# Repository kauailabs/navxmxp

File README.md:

# navX-MXP and navX-Micro Robotics Navigation Sensors
For all documentation and support for navX-MXP, please visit the [navX-MXP Wiki](http://navx-mxp.kauailabs.com).
<p>
For all documentation and support for navX-Micro, please visit the [navX-Micro Wiki](http://navx-micro.kauailabs.com).
<p>
Latest Release Notes are [here](https://github.com/kauailabs/navxmxp/blob/master/ReleaseNotes.md).

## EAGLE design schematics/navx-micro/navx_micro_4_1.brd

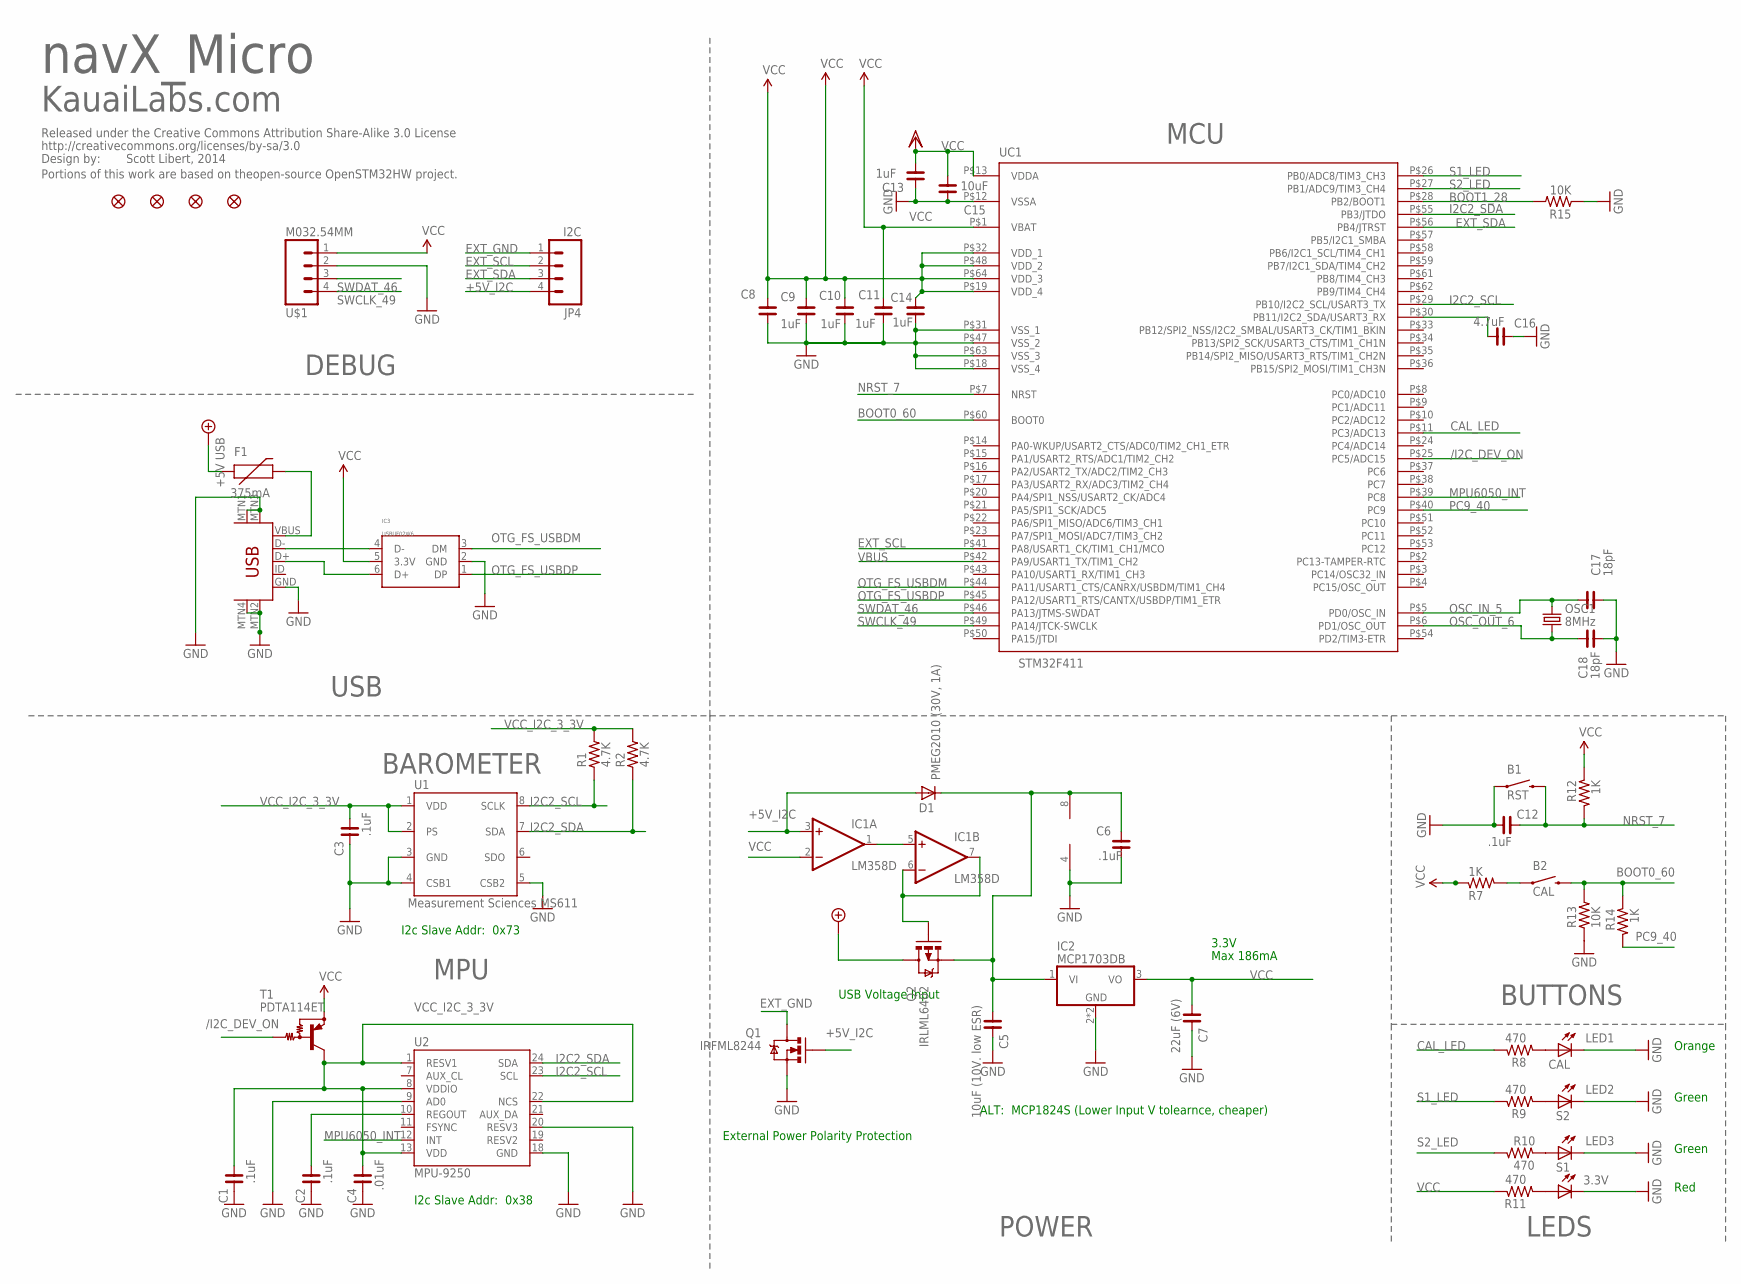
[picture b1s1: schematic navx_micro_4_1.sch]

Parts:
B1: RST; TACTILE-SWITCH-1101NE
B2: CAL; TACTILE-SWITCH-1101NE
C1, C2, C6, C12: .1uF; C0603
C3: .1uF; C0603; DIGIKEY_PART_NUMBER 399-1096-1-ND
C4: .01uF; C0603
C5: 10uF (10V. low ESR); C0805; DIGIKEY_PART_NUMBER 399-1158-1-ND
C7: 22uF (6V); C0805; DIGIKEY_PART_NUMBER 399-1158-1-ND
C8: 1uF; C0603; DIGIKEY_PART_NUMBER 399-3118-1-ND
C9, C10, C11, C13, C14: 1uF; C0603
C15: 10uF; C0805
C16: 4.7uF; C0603
C17, C18: 18pF; C0603
D1: PMEG2010 (30V, 1A); SOD-323
F1: 375mA; 0603
IC1: LM358D; SO08
IC2: MCP1703DB; DIGIKEY_PART_NUMBER MCP1703T-3302E/DBCT-ND
IC3: USBUF02W6; SC70-6; DIGIKEY_PART_NUMBER 497-3743-1-ND
JP4: I2C; 1X04
JP21, JP22, JP23, JP24: FIDUCIAL1X2; FIDUCIAL-1X2
LED1: CAL; CHIP-LED0603
LED2: S2; CHIP-LED0603
LED3: S1; CHIP-LED0603
LED4: 3.3V; CHIP-LED0603
LICENSE_TEXT: CREATIVE_COMMONS
OSC1: 8MHz; CRYSTAL-SMD-5X3
Q1: IRFML8244; SOT23; DIGIKEY_PART_NUMBER DMN3404LDICT-ND
Q2: IRLML6402; SOT23-3
R1, R2: 4.7K; R0603
R7, R12, R14: 1K; R0603
R8, R9, R10, R11: 470; R0603
R13, R15: 10K; R0603
T1: PDTA114ET; SOT23-3
U1: Measurement Sciences MS611; MS5611; DIGIKEY_PART_NUMBER MPL115A2-ND
U2: MPU-9250; QFN24_3MM_INVENSENSE; DIGIKEY_PART_NUMBER 1428-1019-1-ND
U$1: M032.54MM; 1X04_NO_SILK
UC1: STM32F411; TQFP-10X10-64; DIGIKEY_PART_NUMBER 497-11154-ND
USB: Mini-USB; USB-MINIB; DIGIKEY_PART_NUMBER 151-1206-1-ND

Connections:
+5V: F1.1, Q2.3 (D)
+5V_I2C: D1.A, IC1.3 (+IN), JP4.4, Q1.1 (G)
/I2C_DEV_ON: T1.1 (B), UC1.P$25 (PC5/ADC15)
BOOT0_60: B2.P$2 (2), R13.2, R14.1, UC1.P$60 (BOOT0)
BOOT1_28: R15.2, UC1.P$28 (PB2/BOOT1)
CAL_LED: R8.1, UC1.P$11 (PC3/ADC13)
EXT_GND: JP4.1, Q1.3 (D)
EXT_SCL: JP4.2, UC1.P$41 (PA8/USART1_CK/TIM1_CH1/MCO)
EXT_SDA: JP4.3, UC1.P$56 (PB4/JTRST)
GND: B1.P$1 (1), C1.2, C2.2, C3.2, C4.2, C5.2, C6.1, C7.2, C8.1, C9.1, C10.1, C11.1, C12.1, C13.1, C14.1, C15.2, C16.1, C17.1, C18.1, IC1.4 (V-), IC2.2 (GND), IC2.4 (GND), IC3.2 (GND), LED1.C, LED2.C, LED3.C, LED4.C, Q1.2 (S), R13.1, R15.1, U1.3 (GND), U1.4 (CSB1), U1.5 (CSB2), U2.9 (AD0), U2.18 (GND), U2.20 (RESV3), U$1.2, UC1.P$12 (VSSA), UC1.P$18 (VSS_4), UC1.P$31 (VSS_1), UC1.P$47 (VSS_2), UC1.P$63 (VSS_3), USB.GND, USB.MTN1 (MTN2), USB.MTN2 (MTN3), USB.MTN3 (MTN1), USB.MTN4
I2C2_SCL: R1.1, U1.8 (SCLK), U2.23 (SCL), UC1.P$29 (PB10/I2C2_SCL/USART3_TX)
I2C2_SDA: R2.1, U1.7 (SDA), U2.24 (SDA), UC1.P$55 (PB3/JTDO)
MPU6050_INT: U2.12 (INT), UC1.P$39 (PC8)
unnamed: C2.1, U2.10 (REGOUT)
unnamed: B2.P$1 (1), R7.2
unnamed: LED3.A, R10.1
unnamed: C16.2, UC1.P$30 (PB11/I2C2_SDA/USART3_RX)
unnamed: LED2.A, R9.2
unnamed: C5.1, C6.2, D1.C, IC1.8 (V+), IC2.1 (VI), Q2.2 (S)
unnamed: IC1.1 (OUT), IC1.5 (+IN)
unnamed: IC1.6 (-IN), IC1.7 (OUT), Q2.1 (G)
unnamed: LED1.A, R8.2
unnamed: IC3.4 (D-), USB.D-
unnamed: IC3.6 (D+), USB.D+
unnamed: LED4.A, R11.2
NRST_7: B1.P$2 (2), C12.2, R12.2, UC1.P$7 (NRST)
OSC_IN_5: C17.2, OSC1.3 (2), UC1.P$5 (PD0/OSC_IN)
OSC_OUT_6: C18.2, OSC1.1, UC1.P$6 (PD1/OSC_OUT)
OTG_FS_USBDM: IC3.3 (DM), UC1.P$44 (PA11/USART1_CTS/CANRX/USBDM/TIM1_CH4)
OTG_FS_USBDP: IC3.1 (DP), UC1.P$45 (PA12/USART1_RTS/CANTX/USBDP/TIM1_ETR)
PC9_40: R14.2, UC1.P$40 (PC9)
S1_LED: R9.1, UC1.P$26 (PB0/ADC8/TIM3_CH3)
S2_LED: R10.2, UC1.P$27 (PB1/ADC9/TIM3_CH4)
SWCLK_49: U$1.4, UC1.P$49 (PA14/JTCK-SWCLK)
SWDAT_46: U$1.3, UC1.P$46 (PA13/JTMS-SWDAT)
VBUS: F1.2, UC1.P$42 (PA9/USART1_TX/TIM1_CH2), USB.VBUS
VCC: C7.1, C8.2, C9.2, C10.2, C11.2, C13.2, C14.2, C15.1, IC1.2 (-IN), IC2.3 (VO), IC3.5 (3.3V), R7.1, R11.1, R12.1, T1.2 (E), U$1.1, UC1.P$1 (VBAT), UC1.P$13 (VDDA), UC1.P$19 (VDD_4), UC1.P$32 (VDD_1), UC1.P$48 (VDD_2), UC1.P$64 (VDD_3)
VCC_I2C_3_3V: C1.1, C3.1, C4.1, R1.2, R2.2, T1.3 (C), U1.1 (VDD), U1.2 (PS), U2.1 (RESV1), U2.8 (VDDIO), U2.13 (VDD), U2.22 (NCS)

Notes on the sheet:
BAROMETER
MPU
3.3V
Max 186mA
POWER
BUTTONS
LEDS
USB
MCU
KauaiLabs.com
Scott Libert, 2014
Portions of this work are based on theopen-source OpenSTM32HW project.
navX_Micro
I2c Slave Addr: 0x38
I2c Slave Addr: 0x73
ALT: MCP1824S (Lower Input V tolearnce, cheaper)
Orange
Green
Red
USB Voltage Input
DEBUG
External Power Polarity Protection

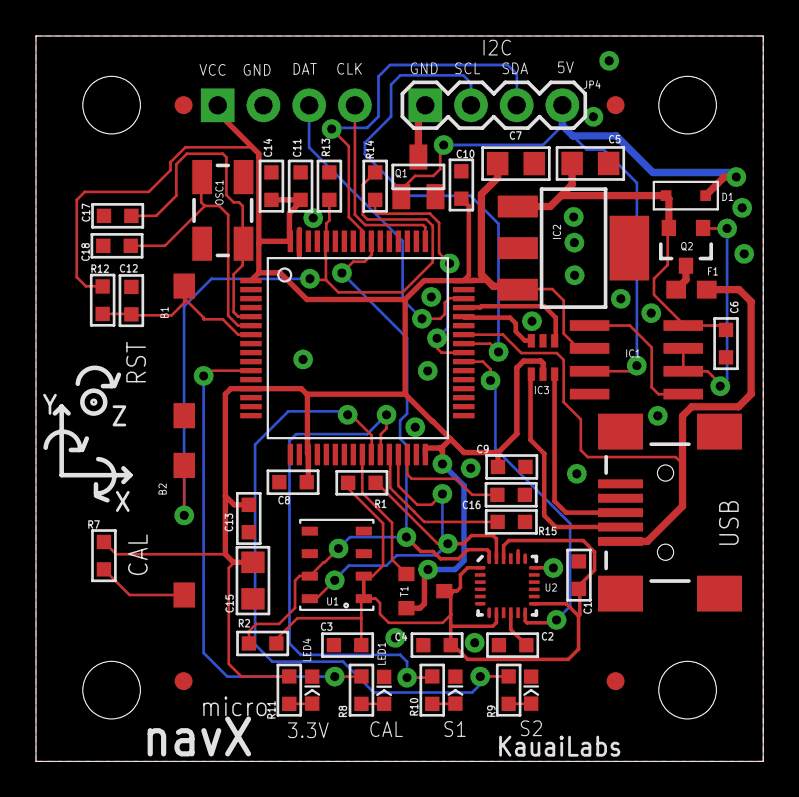
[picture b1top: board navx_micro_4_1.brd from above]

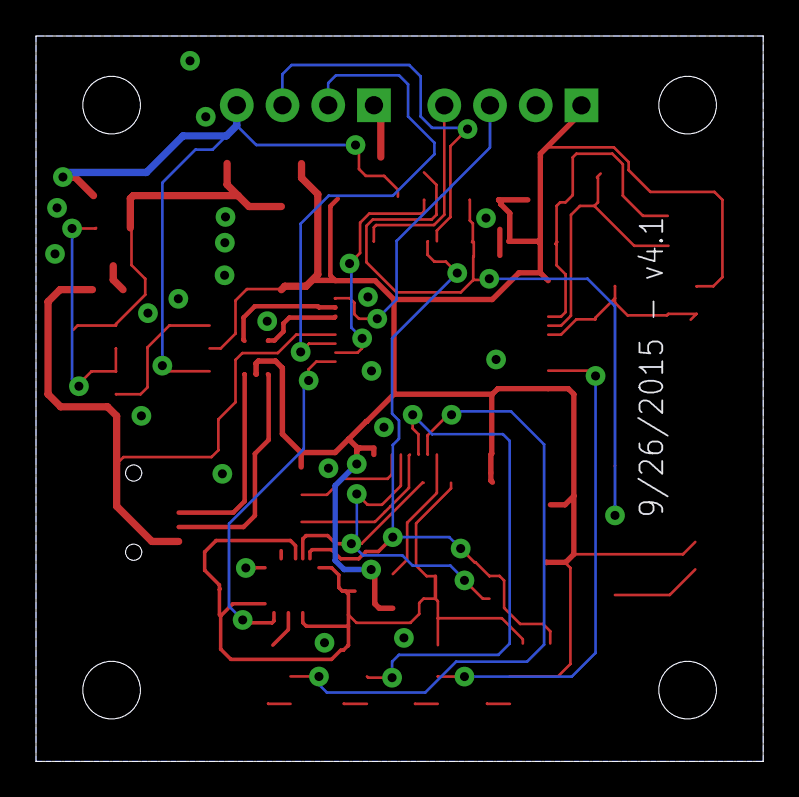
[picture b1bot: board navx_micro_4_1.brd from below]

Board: 2 copper layers, 40.4 x 40.3 mm, 59 parts (2 on the bottom side), 38 nets.

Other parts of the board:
U$2, U$3, U$4, U$7: MXP_STANDOFF_REAR

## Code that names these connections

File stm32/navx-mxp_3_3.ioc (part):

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Mcu.Name=STM32F411R(C-E)Tx
Mcu.Package=LQFP64
Mcu.UserName=STM32F411RCTx
PA11.Mode=Device_Only
PA11.Signal=USB_OTG_FS_DM
PA12.Mode=Device_Only
PA12.Signal=USB_OTG_FS_DP
PA13.Mode=Serial-Wire
PA13.Signal=SYS_JTMS-SWDIO
PA14.Mode=Serial-Wire
PA14.Signal=SYS_JTCK-SWCLK
PA15.Mode=NSS_Signal_Hard
PA15.Signal=SPI1_NSS
PA5.Mode=Full_Duplex_Master
PA5.Signal=SPI1_SCK
PA6.Mode=Full_Duplex_Master
PA6.Signal=SPI1_MISO
PA7.Mode=Full_Duplex_Master
PA7.Signal=SPI1_MOSI
PA8.Mode=I2C
PA8.Signal=I2C3_SCL
PB0.GPIOParameters=GPIO_Label,GPIO_ModeDefaultOutputPP,GPIO_Speed,GPIO_PuPd
PB0.GPIO_Label=LED_S1
PB0.GPIO_ModeDefaultOutputPP=GPIO_MODE_OUTPUT_PP
PB0.GPIO_PuPd=GPIO_NOPULL
PB0.GPIO_Speed=GPIO_SPEED_LOW
PB0.Signal=GPIO_Output
PB1.GPIOParameters=GPIO_Label,GPIO_ModeDefaultOutputPP,GPIO_Speed,GPIO_PuPd
PB1.GPIO_Label=LED_S2
PB1.GPIO_ModeDefaultOutputPP=GPIO_MODE_OUTPUT_PP
PB1.GPIO_PuPd=GPIO_NOPULL
PB1.GPIO_Speed=GPIO_SPEED_LOW
PB1.Signal=GPIO_Output
PB10.Mode=I2C
PB10.Signal=I2C2_SCL
PB14.GPIOParameters=GPIO_Label,GPIO_PuPd,GPIO_Mode
PB14.GPIO_Label=SPI_ENABLE
PB14.GPIO_Mode=GPIO_MODE_INPUT
PB14.GPIO_PuPd=GPIO_NOPULL
PB14.Signal=GPIO_Input
PB15.GPIOParameters=GPIO_Label,GPIO_PuPd,GPIO_Mode
PB15.GPIO_Label=UART_ENABLE
PB15.GPIO_Mode=GPIO_MODE_INPUT
PB15.GPIO_PuPd=GPIO_NOPULL
PB15.Signal=GPIO_Input
PB3.Mode=I2C
PB3.Signal=I2C2_SDA
PB4.Mode=I2C
PB4.Signal=I2C3_SDA
PC3.GPIOParameters=GPIO_ModeDefaultOutputPP,GPIO_Label,GPIO_Speed,GPIO_PuPd
PC3.GPIO_Label=CAL_LED
PC3.GPIO_ModeDefaultOutputPP=GPIO_MODE_OUTPUT_PP
PC3.GPIO_PuPd=GPIO_NOPULL
PC3.GPIO_Speed=GPIO_SPEED_LOW
PC3.Signal=GPIO_Output
PC5.GPIOParameters=GPIO_Label,GPIO_ModeDefaultOutputPP,GPIO_Speed,GPIO_PuPd
PC5.GPIO_Label=/I2C_DEV_ON
PC5.GPIO_ModeDefaultOutputPP=GPIO_MODE_OUTPUT_PP
PC5.GPIO_PuPd=GPIO_NOPULL
PC5.GPIO_Speed=GPIO_SPEED_LOW
PC5.Signal=GPIO_Output
PC6.Mode=Asynchronous
PC6.Signal=USART6_TX
PC7.Mode=Asynchronous
PC7.Signal=USART6_RX
PC8.GPIOParameters=GPIO_Label,GPIO_PuPd,GPIO_Mode
PC8.GPIO_Label=MPU_INT
PC8.GPIO_Mode=GPIO_MODE_INPUT
PC8.GPIO_PuPd=GPIO_NOPULL
PC8.Signal=GPIO_Input
PC9.GPIOParameters=GPIO_Label,GPIO_PuPd,GPIO_Mode
PC9.GPIO_Label=CAL_BTN
PC9.GPIO_Mode=GPIO_MODE_INPUT
PC9.GPIO_PuPd=GPIO_NOPULL
PC9.Signal=GPIO_Input
PH0\ -\ OSC_IN.Mode=HSE-External-Oscillator
PH0\ -\ OSC_IN.Signal=RCC_OSC_IN
PH1\ -\ OSC_OUT.Mode=HSE-External-Oscillator
PH1\ -\ OSC_OUT.Signal=RCC_OSC_OUT
RCC.HSEState-ClockTree=RCC_HSE_ON
RCC.HSE_VALUE=8000000
RCC.SYSCLKFreq_VALUE=96000000
RCC.SYSCLKSource=RCC_SYSCLKSOURCE_PLLCLK

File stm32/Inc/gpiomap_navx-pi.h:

/**
  ******************************************************************************
  * File Name          : mxconstants.h
  * Description        : This file contains the common defines of the application
  ******************************************************************************
  *
  * COPYRIGHT(c) 2016 STMicroelectronics
  *
  * Redistribution and use in source and binary forms, with or without modification,
  * are permitted provided that the following conditions are met:
  *   1. Redistributions of source code must retain the above copyright notice,
  *      this list of conditions and the following disclaimer.
  *   2. Redistributions in binary form must reproduce the above copyright notice,
  *      this list of conditions and the following disclaimer in the documentation
  *      and/or other materials provided with the distribution.
  *   3. Neither the name of STMicroelectronics nor the names of its contributors
  *      may be used to endorse or promote products derived from this software
  *      without specific prior written permission.
  *
  * THIS SOFTWARE IS PROVIDED BY THE COPYRIGHT HOLDERS AND CONTRIBUTORS "AS IS"
  * AND ANY EXPRESS OR IMPLIED WARRANTIES, INCLUDING, BUT NOT LIMITED TO, THE
  * IMPLIED WARRANTIES OF MERCHANTABILITY AND FITNESS FOR A PARTICULAR PURPOSE ARE
  * DISCLAIMED. IN NO EVENT SHALL THE COPYRIGHT HOLDER OR CONTRIBUTORS BE LIABLE
  * FOR ANY DIRECT, INDIRECT, INCIDENTAL, SPECIAL, EXEMPLARY, OR CONSEQUENTIAL
  * DAMAGES (INCLUDING, BUT NOT LIMITED TO, PROCUREMENT OF SUBSTITUTE GOODS OR
  * SERVICES; LOSS OF USE, DATA, OR PROFITS; OR BUSINESS INTERRUPTION) HOWEVER
  * CAUSED AND ON ANY THEORY OF LIABILITY, WHETHER IN CONTRACT, STRICT LIABILITY,
  * OR TORT (INCLUDING NEGLIGENCE OR OTHERWISE) ARISING IN ANY WAY OUT OF THE USE
  * OF THIS SOFTWARE, EVEN IF ADVISED OF THE POSSIBILITY OF SUCH DAMAGE.
  *
  ******************************************************************************
  */
/* Includes ------------------------------------------------------------------*/

/* USER CODE BEGIN Includes */

/* USER CODE END Includes */

/* Private define ------------------------------------------------------------*/

#define NAVX_2_RPI_SPI_Comm_Ready_Pin GPIO_PIN_2
#define NAVX_2_RPI_SPI_Comm_Ready_GPIO_Port GPIOE
#define S2_LED_Pin GPIO_PIN_2
#define S2_LED_GPIO_Port GPIOC
#define S1_LED_Pin GPIO_PIN_3
#define S1_LED_GPIO_Port GPIOC
#define BOOT1_Pin GPIO_PIN_2
#define BOOT1_GPIO_Port GPIOB
#define _CAN_INT_Pin GPIO_PIN_4
#define _CAN_INT_GPIO_Port GPIOB
#define _I2C_DEV_ON_Pin GPIO_PIN_12
#define _I2C_DEV_ON_GPIO_Port GPIOE
#define CAN_CS_Pin GPIO_PIN_12
#define CAN_CS_Port GPIOB
#define MPU9250_INT_Pin GPIO_PIN_8
#define MPU9250_INT_GPIO_Port GPIOD
#define CAL_LED_Pin GPIO_PIN_9
#define CAL_LED_GPIO_Port GPIOD
#define CAN_STANDBY_Pin GPIO_PIN_11
#define CAN_STANDBY_GPIO_Port GPIOD
#define CAL_BTN_Pin GPIO_PIN_10
#define CAL_BTN_GPIO_Port GPIOD
#define _CAN_RESET_Pin GPIO_PIN_10
#define _CAN_RESET_GPIO_Port GPIOC

/* USER CODE BEGIN Private defines */
#define QE1_A_Pin GPIO_PIN_9  //PE9,  TIM1 CH1
#define QE1_A_GPIO_Port GPIOE
#define QE1_B_Pin GPIO_PIN_11 //PE11, TIM1 CH2
#define QE1_B_GPIO_Port GPIOE
#define QE2_A_Pin GPIO_PIN_15 //PA15, TIM2 CH1
#define QE2_A_GPIO_Port GPIOA
#define QE2_B_Pin GPIO_PIN_3  //PB3,  TIM2 CH2
#define QE2_B_GPIO_Port GPIOB
#define QE3_A_Pin GPIO_PIN_6  //PC6,  TIM3 CH1
#define QE3_A_GPIO_Port GPIOC
#define QE3_A_Second_Pin GPIO_PIN_2   /* To avoid EXTI conflict w/PWM_GPIO4 */
#define QE3_A_Second_GPIO_Port GPIOD  /* To avoid EXTI conflict w/PWM_GPIO4 */
#define QE3_B_Pin GPIO_PIN_7  //PC7,  TIM3 CH2
#define QE3_B_GPIO_Port GPIOC
#define QE4_A_Pin GPIO_PIN_12 //PD12, TIM4 CH1
#define QE4_A_GPIO_Port GPIOD
#define QE4_B_Pin GPIO_PIN_13 //PD13, TIM4 CH2
#define QE4_B_GPIO_Port GPIOD
#define QE5_A_Pin   GPIO_PIN_0 //PA0, TIM5 CH1
#define QE5_A_GPIO_Port GPIOA
#define QE5_B_Pin   GPIO_PIN_1 //PA1, TIM5 CH2
#define QE5_B_GPIO_Port GPIOA
#define PWM_GPIO3_Pin GPIO_PIN_5 //PE5, TIM9 CH1
#define PWM_GPIO3_GPIO_Port GPIOE
#define PWM_GPIO4_Pin GPIO_PIN_6 //PE6, TIM9 CH2
#define PWM_GPIO4_GPIO_Port GPIOE

// Note:  UNUSED EXTI INTERRUPT CHANNELS:  4, 8, 10, 14

#define COMM_OE2_Pin GPIO_PIN_2
#define COMM_OE2_GPIO_Port GPIOA

/* IOCX Interrupt Signal */
#define NAVX_2_RPI_INT4_Pin GPIO_PIN_10
#define NAVX_2_RPI_INT4_GPIO_Port GPIOA

/* AHRS Interrupt Signal */
#define NAVX_2_RPI_INT2_Pin GPIO_PIN_8
#define NAVX_2_RPI_INT2_GPIO_Port GPIOC

#define EEPROM_WP_Pin GPIO_PIN_11
#define EEPROM_WP_GPIO_Port GPIOC

#define _RPI_GPIO_OE1_Pin GPIO_PIN_3
#define _RPI_GPIO_OE1_GPIO_Port GPIOE

#define _RPI_GPIO_OE2_Pin GPIO_PIN_4
#define _RPI_GPIO_OE2_GPIO_Port GPIOE

#define EXT_PWR_SWITCH_ON_Pin GPIO_PIN_7
#define EXT_PWR_SWITCH_ON_GPIO_Port GPIOB

#define RPI_GPIO_DIR_IN_Pin GPIO_PIN_8
#define RPI_GPIO_DIR_IN_GPIO_Port GPIOB

/* CAN Interrupt Signal */
#define NAVX_2_RPI_INT3_Pin GPIO_PIN_1
#define NAVX_2_RPI_INT3_GPIO_Port GPIOD

#define _IO_POWER_FAULT_Pin GPIO_PIN_4
#define _IO_POWER_FAULT_GPIO_Port GPIOD

#define _CAN_RX0BF_Pin GPIO_PIN_14
#define _CAN_RX0BF_GPIO_Port GPIOD

#define _CAN_RX1BF_Pin GPIO_PIN_15
#define _CAN_RX1BF_GPIO_Port GPIOD

#define CAN_OK_LED_Pin GPIO_PIN_15
#define CAN_OK_LED_GPIO_Port GPIOE

/* VMX-pi Board Rev 5.38 added:
 *
 * PD 7, 6 and 5:  3 bits of board Revision, as follows:
 * - 0x111:   Boards previous to v. 5.38 (e.g., 5.35 [Nov. 2017]
 * - 0x110:   Revision 5.38 [Nov, 2018]
 *
 * NOTE:  PD7 is the most significant bit.
 *
 * NOTE:  These signals were disconnected in previous designs.  They can be
 * tested on all designs by pulling them high at startup and reading their state.
 */

#define VMXPI_BOARDREV_BIT2_Pin GPIO_PIN_7
#define VMXPI_BOARDREV_BIT1_Pin GPIO_PIN_6
#define VMXPI_BOARDREV_BIT0_Pin GPIO_PIN_5
#define VMXPI_BOARDREV_Port GPIOD

#define VMXPI_BOARDREV_MAX  0x07
#define VMXPI_BOARDREV_5_35	0x07  /* NOTE:  All pins disconnected on this revision. */
#define VMXPI_BOARDREV_5_38 0x06  /* BIT2, BIT 1 Disconnected.  BIT 2 Pulled to Ground. */
								  /* NOTE:  Bit 2 is not actually pulled to Ground.  So */
								  /*        there is no known reliable method to detect */
								  /*        this board version.  Fortunately, control of*/
								  /*        the 5.38 functionality is backwards-        */
								  /*        compatible.                                 */

/* VMX-pi Board Rev 5.38 added:
 * Output Enable Pin for output-direction CommDIO Signals:
 * - UART: TX
 * - SPI:  CLK CS MOSI
 * This signal is active low.
 * This signal was unconnected in previous designs.
 */

#define _COMM_OE1_Pin GPIO_PIN_3
#define _COMM_OE1_GPIO_Port GPIOA

/* USER CODE END Private defines	 */

#define GPIO_INT(GPIO_INT_NUM) (1 << GPIO_INT_NUM)


/**
  * @}
  */ 

/**
  * @}
*/ 

/************************ (C) COPYRIGHT STMicroelectronics *****END OF FILE****/

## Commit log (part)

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2015-12-21 Fixed bug in encodeProtocolFloat()
    The previous code was writing 8 bytes (the final being a NULL character)
    rather than 7 (the size of a protocol float). As a result, when
    formatting packets a buffer overflow condition could exist.
2015-12-21 Fixed typo in revision description.
2015-12-23 Added code to set self test status complete as part of the factory calibration routine.
2015-12-24 Fixed some run-time issues w/a few of the Java navX-MXP examples.
    Previously, the Java samples were using the 2-parameter constructor for
    the RobotDrive class; they were changed to use the 4-parameter
    constructor which is the correct constructor when used with Mecanum
    drive sytsems, which is intended in the examples.
2016-01-08 Address some issues in the AHRS class
    - Fixed issue w/getDisplacementX/Y returning incorrect values when used
    with older firmware versions.
    - Removed some unnecessary synchronization statements.
2016-01-15 updating FRC900 LabView Library to Latest
2016-02-21 Fixed issue w/ContinuousAngleTracker; added LastSensorTimestamp
2016-04-23 Increased supported update rate to 100Hz. Also, checked in an updated .h file that got missed during the last checkin.
2016-04-26 Updated to FRC900 LabVIEW library v.2.3.254.
2016-05-19 Updated version number to 3.0
    Also modified RegisterIO.java to allow 200Hz operation.
2016-05-20 Fixed truncation issue in quaternion handling in get_dmp_data
2016-05-25 Updated to latest (16.2.09) version of ftcapp.
2016-09-02 Updated navX_ftc to use the 2016 beta 2.0 libraries. Also updated OpModes to be compliant with 2016 FTC beta 2.0 library conventions.
2016-11-06 Eclipse changes to settings/language.settings.xml files.
2016-11-06 FRC NavX Java Library build improvements
    Removed previous dependency on Java 7; fixed paths to base navx java
    library.
2016-11-06 FTC Library Modifications
    Updated version of FTC library to use.
2016-11-23 A few more updates for WPI LIbrary 2017 Compatibility.
2016-11-24 Updated java wpilib example projects to remove "userLibs" enrtry from build.properties file.
2016-12-09 Working on LabVIEW Menus
2016-12-11 Revert "Fix changelog"
    This reverts commit d251cd37bd034f8f5f1789a11d561dfdf5b8f348.
2016-12-15 Modified Java AHRS class to notify of yaw reset on receipt of yaw reset complete command.
    Also modifed AHRSProtocol.java to fix a bug in the identifier (msg id)
    for the Integration Control Response Packet.
2016-12-29 Restore AutoBalance example to original state
    Back in August, the content of the AutoBalance.java file was replaced
    w/the content from the CollisionDetection example; now this is fixed.
2017-01-01 Ensure that write packets don't contain NULL characters
    This is a workaround for an issue found in the WPI Library SerialPort
    Write() method. Note: This should be replaced w/the new WPI Libary
    Write API which allows embedded NULL characters in strings.
2017-01-01 I added a table lookup to SPI CRC
    I added a table lookup to the CRC. It seems muck faster.
2017-01-06 Updated comments in FRC Java Examples.
2017-01-12 Created rpi directory; added based communication management classes.
2017-01-16 Update to help with USB Lock-up issue
    I changes the zero notifier:
    I added code to make the action engine look for a change to fire the
    notifier to the main loop.
    I added code to make it so the operator can only fire a zero notifier at
    1 second intervals.
    I changed the way the loops are metered to get to the desitred loop
2017-01-17 Added new Release notes document
2017-01-30 Added new FRC RoboRIO Java "RotateToAngle_Tank" example
2017-02-10 Checkpoint navX-PI current state.
2017-02-20 Added struct packing to a few key structures.
2017-02-26 Removed the expansion IO from examples
    I removed the expansion IO older version from the example file. I want o
    make sure that no one tries to use the old system.
2017-06-11 updated CAN register public interface, modified CAN logic for 24Mhz crystal
2017-06-15 Added code to set ide flag correction in pack_xxx_id() functions.
2017-06-20 rpi interface bug fixing
2017-06-25 Fix bug in CTL_TXB Macro that was causing writes to TX buffers 1/2 to fail.
2017-06-26 CAN code cleanup; added Tx/Rx Fifo flush feature.
2017-06-26 Added CAN transceiver/controller reset support.
2017-06-27 Updated HAL power header.
2017-06-28 Add definition for number of interrupts.
2017-06-28 Renamed "spi_comm.h" to "CommCtrl.h"
2017-07-09 Updated capability bits in header; removed 4 GPIOs.
2017-07-15 Added access to RPI GPIO Input/Ouput selection jumper, and scale ADC voltages by 3.3V/5V select.
2017-07-15 Added initialization for new GPIOs added in board rev v5.30.
2017-07-19 Delete Readme.txt.txt
    Delete improperly named readme
2017-07-23 Migrated analog inputs to MISC register bank.
2017-07-29 Checkpoint, 7/29/2017
2017-08-06 Fixed some CAN error recovery issues; added bus_off_count and tx_full_count registers to CAN register bank.
2017-08-12 Resolved re-entrant communication issue which was causing sporadic CAN communication failures.
2017-08-23 Checkpoint navx-pi changes.
2017-08-30 Restore erroneously-deleted files.
2017-09-03 Incorporated PIGPIO library directly into the HAL library; modifed installation directory name.
2017-09-03 Removed issue causing 'comment' warnings.
2017-09-04 Added makefiles for all example projects.
2017-11-08 Fixed bug in maven deployment script.
2017-11-18 Updated RegisterIOSPI.cpp to match change to use wpi::mutex from RegisterIOI2C.cpp (pull request by Peter Mitrano, WPI)
2017-11-25 Removed board test startup code; fixed bug in RTC Clock configuration.
2017-12-14 Modified example programs to match the removal of the LiveWIndow.
2017-12-26 Added V1 VMX-pi enclosure STP/STL files and updated makedist_vmx.bat to copy it correctly.
2018-01-13 Updated maven POM to indicate dependency upon 2018.1.1 verison of wpilib-java.
2018-05-19 Fixed issue with PWM Capture Support.
2018-07-07 Fix bug in programming of filter registers 4, 5 and 6. Add read-back of filter registers after writing.
2018-08-30 Add code signing
2018-11-03 Support 2019 Beta build - add gradle java/c++ compilation support
2018-11-05 Updated labview vi install location to 2018 version of LabView.
2018-11-08 More bugfixing related to MavenCentral publishing
2018-11-28 Bug fix in IOCXRegisters.h/IOCXExRegisters.h
2018-12-01 Updated comments to clarify how GPIO pulse lengths are specified.
2018-12-13 Added support for timer counter reset triggering by GPIO interrupts.
2018-12-19 Updated vendordeps file to latest version (WPILib Beta 4)
2018-12-31 - Modified comments on MISC Register structure for accumulator counters.
2019-01-04 Built against WPI Library 2019.1.1 Kickoff Release.
2019-01-28 Updated project file to property execute the upload script
    New Invocation: C:\Windows\System32\cmd.exe /c
    ..\upload_navx-mxp_bin.bat ${ConfigurationName}
2019-01-31 Updated ST Micro "DFU" DLLs to latest version (3.0.6.0).
    These required updating since in some cases they cause trouble on
    Windows 10 systems; the older DLLs referenced versions of the MSVC
    runtime dlls in the side-by-side configuration directory that were
    incompatible on certain customer systems.
2019-01-31 Fixup documentation to address javadoc warnings.
2019-02-01 Added some debug tracing messages (only if logging is enabled) and also added exception handlers when invoking the SerialPort Reset() method
    The reset() method sometimes throws an unclean status exception, and so
    code was added to close/reopen the serial port if this ever occurs.
2019-02-02 Adjusted the ZeroYaw messages in the case where Startup Calibration is still in progress.
2019-02-02 Fixed a bug in the rate-limiting of I2C error logging.
2019-02-02 Small fixes to firmware and C++ Library
    - Changed default USB protocol to MSGID_AHRSPOS_UPDATE (previously was
    MSGID_AHRSPOS_TS_UPDATE) due to the fact that the RoboRIO LabVIEW
    libraries dont' decode the MSGID_AHRSPOS_TS_UPDATE correctly.
    - Correctly condition to C++ AHRS class logging_enabled flag when
    EnableLogging() is invoked.
2019-05-06 Modified Quad Encoder initialization to always set the prescaler to 0, since in this case the internal clock is not used.
2019-05-11 Updated VCP drivers to work correctly on recent Windows 10 builds. Updated DFU files to include Visual Studio 2013 redistributable files. Updated installers to match.
2019-05-22 Updated CAN interrupt timestamping to be more precise.
2019-06-10 Upated VMX build process to create Release (rather than Debug) builds of the VMX-pi firmware.
2019-07-02 Added Access to embedded navX-sensor on VMX-pi (Raspbian-only) platforms when SPI/I2C/SerialPort.Port.kMXP is requested. Dependencies: C++: dependent upon the AHRS_Mau C-style interface present in li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
2019-07-02 Fixed some bugs in publishing of linuxraspbian artifacts to maven
2019-07-07 Rename Shared Library from libwpiHalMau?.so to libwpiHal?.so
2019-07-17 Fixed bug in vmx-pi installer's reference to the firmware updater tool.
2019-10-05 - Added new VMX-pi enclosure design files for Raspberry Pi 4 - Added VS2008 SP1 redistributable, and invocation by installer
2019-10-14 Fixed up some issues with navX-Micro build.gradle file for SkyStone version of FTC SDK (for 2019 Season).
2019-10-25 Updated setup to install maven artifacts to C:\User\Public\wpilib\2020, using the updated convention for the 2020 season.
2019-10-31 Fixed path error in navX-MXP/navX-Micro installer scripts.
2019-11-14 Fixed path error in installation location for C++ Expansion IO VSCode Example.
2019-12-01 Add creation of signing (asc) file for new ".module" file.
2019-12-10 - Modified GUID for navx-micro app in installer, to disambiguate from navX-MXP & VMX-pi. - Modified GUID for vmx-pi app in installer, to disambiguate from navX-MXP & navX-Micro.
2020-01-25 Checkin version matching the V1.5 release
2020-01-30 Updated navx WPI vendordeps template file to includes the windowsx86-64 platform, now that simulation device support is functional.
2020-02-05 Update maven deploy script to hopefully work around some reliability issues encountered during uploads to Sonatype Nexus (Maven Central) Repository.
2020-02-07 Updated enclosure files, fixing some geometry issues and adding STP, 3D-Studio files
2020-07-20 - Updated AHRS class to work with the NavxMicroNavigationSensor class, which works now with the REV Expansion and Control Hubs. - Updated OpMode examples to work with the new AHRS class.
2020-10-09 Updated STMCDC Inf file
2020-11-10 Added "Virtual Counter Mode" Register definitions to IOCXEXRegisters
2021-01-23 Added discrete I2C, SPI and UART examples
2021-01-28 Updated C# projects to use the newly-updated KauaiLabs signing certificate.
2021-02-14 Add Official Gradle Wrapper Validation Action
    Adds github action to validate the gradle-wrapper.jars checksums in the repository.
    See: https://github.com/gradle/wrapper-validation-action
2021-04-27 Added "enable = false" for all Gradle tasks withType(GenerateModuleMetadata) Added as recommended by Thad House Added to both Java and C++ Builds
2021-10-26 - Added additional synchronization to CAN_ISR_FlagFunction() - Modified CAN Message send to use the RTS command, which should eliminate unexpeceted retransmission of messages (see errata sheet)
2021-12-30 To minimize possible noise sources: - Lowered output GPIO speeds to Low (Max 10Hz) for all, except for SPI interfaces, which were lowered to MEDIUM (max 25Mhz) speed
2022-05-07 - Fixed DFU Driver installer to work on Windows11 (uses new STM32CubeProgrammer installer)

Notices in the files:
parts and their libraries:
SparkFun: Released under the Creative Commons Attribution Share-Alike 3.0 License
SparkFun: http://creativecommons.org/licenses/by-sa/3.0
SparkFun-Connectors: Licensing: CC v3.0 Share-Alike You are welcome to use this library for commercial purposes.
